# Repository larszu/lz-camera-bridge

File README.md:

# LZ Camera Bridge

A universal camera-control hub. One software interface — a broadcast-style
**RCP** (paint controls) and a touch **PTZ panel** modelled on the Panasonic
AW‑RP150 — plus a normalizing **command bus** that drives cameras from many
vendors over their native protocols. The same commands also reach every camera
from a Bitfocus **Companion** surface or a USB **control panel**.

> **Status:** the bridge, protocols and UI are real and build clean; a
> committed unit-test suite covers the protocol framing. Where a family was
> verified against public docs or an official reference it is marked
> **verified** below. Items marked *tuning* need a first on-camera test to
> confirm value encodings. Nothing ships as a fake/demo device.

## Download

**One installation is the whole tool.** The installer for Windows and macOS
carries the control surface *and* the bridge; the bridge starts with the
application, on `ws://localhost:9700`, and stops with it.

**https://github.com/larszu/lz-camera-bridge/releases**

That was not always true, and the difference matters if you read an older note:
until 2026-09-16 the installer shipped the panel alone. It came up looking
complete and reconnected every three seconds against a bridge that nobody had
started — you were expected to run a second process out of a clone of this repo,
and nothing in the application said so. Now the panel finds its bridge because
the application brought it.

A separate bridge is still perfectly legal, and for a control room it is the
normal case: run the bridge where the cameras are and point tablets at it (see
*Other devices on the same network*). If port 9700 is already taken the
application says so and uses the bridge that is already running, instead of
failing silently.

## The web page

Every push to the default branch builds this repo's page from
`.github/workflows/pages.yml` and publishes it:

**https://larszu.github.io/lz-camera-bridge/**

The workflow **asks the Pages API before it configures anything.** With no
Pages site it still builds — that is a real check — and skips only the
publishing step, with a warning and the one missing step in the run summary.
A run that must stay red for a click nobody made teaches people to ignore red.

Measured 2026-09-16: **published.** The Pages site exists, and the `deploy` job
now runs through — the switch that no workflow can flip (`GITHUB_TOKEN` may not
create a site) has been thrown. Every push to `main` publishes by itself.

What the page carries is the README and `docs/`, rendered — **not the UI
itself.** That is deliberate and not an omission: `web-rcp` is a client that
needs the bridge, and on a Pages address it would look like the application
while operating no camera. The running program comes from the installer below.

---
## Supported cameras

| Family | Mode | Transport | Status |
|---|---|---|---|
| Sony CCU (HXC/HDC, BRC) | `tcp` / `serial` | 700PTP over TCP :7700 / RS‑422 | paint verified; AWB/ABB deliberately disabled¹ |
| Sony FX / Alpha (FX3, FX6, A7 …) | `sony-usb` | PTP vendor extension over USB (libusb) | **verified** (codes from libgphoto2); handshake 3.00 and confirmed writes ported³ |
| Sony FX / Alpha over Wi-Fi/LAN | `sony-ptpip` | PTP/IP TCP 15740, SSDP discovery; Access Authentication through SSH (port 22, aes128-ctr, host-key fingerprint) | protocol **verified on an FX3 (fw 7.00)**³; this bridge path read-only on that FX3 |
| Sony Monitor & Control (FX WiFi) | `sony-mnc` | HTTP :10000 + SSDP discovery | unverified (undocumented app protocol) — for FX3/A7 prefer `sony-ptpip` |
| Canon EOS (R5/R6/R7/R8/R10 …) | `canon-ccapi` | CCAPI HTTP REST :8080 | **verified** (official CCAPI) |
| Panasonic Lumix (S1/S5/GH5/GH6 …) | `lumix-http` | `cam.cgi` HTTP | verified |
| Blackmagic (Pocket/Studio/URSA, FW 8.6+) | `blackmagic` | `/control/api/v1` REST + WS | **verified** |
| Z CAM (E2 family) | `zcam` | `/ctrl/set` HTTP | verified |
| Panasonic AW PTZ (AW‑UE/HE) | `panasonic-ptz` | `aw_ptz` / `aw_cam` CGI | **verified** (AW protocol) |
| VISCA over IP (PTZOptics, Marshall, AVer, Sony BRC/SRG) | `visca` | UDP :1259 (raw) / :52381 (Sony header) | **verified** |
| HTTP-CGI PTZ (Vissonic/PTZOptics `ptzctrl.cgi`, Sony SRG/BRC `/command/`) | `http-cgi` | HTTP GET, Referer + Digest; power via VISCA TCP :5678 (Vissonic) or `main.cgi` (Sony) | **verified** live on a Vissonic clone and a Sony SRG-A40 |
| JVC ConnectedCam / KY‑PZ | `jvc` | Digest login + `/cgi-bin/api.cgi` | verified vocabulary (some steps *tuning*) |
| BirdDog NDI PTZ | `birddog` | VISCA :52381 + REST :8080 | verified endpoints (*tuning*) |
| VISCA on a serial line (same heads, RS‑232/422 wiring) | `visca-serial` | RS‑232 8N1, 9600 default, daisy‑chain address 1–7 | framing unit‑tested; *not yet on a camera* |
| DJI Ronin RS 2 / RS 3 Pro | `dji-ronin` | DJI R SDK over CAN 1 Mbit/s via USB SLCAN adapter | framing unit‑tested; *not yet on a gimbal*² |
| DJI Osmo Pocket 3 / 4 | `dji-osmo` | DUML over a serial (CDC) device | framing unit‑tested; *not yet on a gimbal*³ |

³ Sony PTP, shared by `sony-usb` and `sony-ptpip` (`SonyPtpClient`), follows
Sony's *Camera Control PTP 3 Reference*: handshake with protocol 3.00 and
retry while the camera has no version yet; every write waits until the camera
reports the value (a real FX3 shows it ~250 ms late); 500 ms after an
exposure-mode change; the clock (0xD223) as an ISO 8601 string. The protocol
code is the one [lz-camera-sync](https://github.com/larszu/lz-camera-sync)
runs against an FX3 (fw 7.00) since 2026-10-07 — reading 369 properties,
writing and restoring values, setting the clock, over Wi-Fi with SSH. In this
bridge the `sony-ptpip` path was checked read-only against that FX3 (SSDP
found it and an A7 IV; SSH with fingerprint, handshake, 369 properties). The
SSH password is never written to `site.json`; after a bridge restart it is
entered again.

¹ Sony's 700 protocol is NDA-only; no public source documents the auto‑setup
command codes, so those buttons stay disabled rather than guessing at a
broadcast CCU. See `packages/web-rcp/src/capabilities.ts`.

² **RS 2 and RS 3 Pro only.** RS 3 and RSC 2 look the same and do not speak the
SDK. Needs a USB SLCAN adapter (CANable, USBtin, Lawicel) on the focus‑wheel
port — not SocketCAN, which is Linux‑only.

³ DJI publishes no control interface for the Pocket series, and its USB‑C port
serves storage and UVC webcam — **there is no USB control path.** The one
publicly reverse‑engineered route is Bluetooth LE; what ships here is DUML over
a serial device, and the BLE seam is prepared but not filled. Both gimbals move
the head only: a gimbal carries a camera, it is not one, so paint controls stay
greyed out. The full picture, including which constants to turn first if a
device stays silent, is in [`docs/dji-gimbal.md`](docs/dji-gimbal.md).

## Control surfaces

- **Web RCP** — Sony-style paint panel (iris, master black/gamma, R/G/B white &
  black balance, gain, ND, shutter, bars). Buttons are gated per backend so
  unsupported functions are disabled, not silently failing.
- **Touch PTZ panel** — AW‑RP150-style joystick (pan/tilt with speed),
  zoom/focus rockers, push‑AF, iris and a paged preset grid with a store mode.
- **Soft presets** — on heads that position absolutely and report their pose
  (VISCA IP/RS‑232, BirdDog, Panasonic AW, HTTP‑CGI, robotic heads) a stored
  preset keeps the pose in the bridge, and a recall glides there with
  ease‑in/out: all axes start and land together, move time per preset, *Soft*
  switch per preset. Other paths recall the camera's own preset, and the
  panel says so.
- **Bitfocus Companion** — module in `packages/companion-module-lz-camera-bridge`
  (v0.2.0): paint, pan/tilt/zoom/focus and the elevation column, soft presets
  (move time, *Soft* per preset), studio shots (cut/fade, shot sets, seats,
  moves, *move anyway*, on-air lock per camera), panorama aim and the switcher,
  with dropdowns, feedbacks, variables and ready-made button pages built from
  the bridge's cameras and studio shots. It talks to the Companion API
  (9701/9702) and the panel's port (9700). See its
  [`HELP.md`](packages/companion-module-lz-camera-bridge/companion/HELP.md).
- **USB HID control panel** — a data-driven adapter maps a hardware panel's
  axes/buttons onto the command bus, so one panel controls any brand.
- **Keyboard** — on the PTZ panel the arrow keys drive while held, `1`–`9`
  recall presets, `Home` goes home; a window that loses focus stops the head.
- **Planned shots** — the MultiCam Planner's camera list (v3) carries each
  camera's heading and its shots as pan/tilt/focal length in the room frame.
  The bridge turns them into head angles, drives them (`ptzAbsolute` on
  VISCA, Sony CGI, Panasonic AW and the Vissonic heads via VISCA TCP),
  stores them in the head's own preset memory, and takes a one-time
  **offset** on site: steer the head onto one known shot, click *Head is
  here*, and the mounting error is applied to every shot. From then on any
  panel or Companion recalls them by number. Zoom from a focal length is
  estimated between the ends of the lens until a **zoom curve** is measured:
  drive the zoom to 0/25/50/75/100 %, read the focal length off the lens or
  the camera menu, *Record point*. Details in
  [`docs/camera-plan.md`](docs/camera-plan.md).
- **Aim by frame** — on the PTZ panel, drag a 16:9 frame in the camera's live
  picture: the bridge turns it into pan/tilt from the pose the head reports
  and into a zoom position from the field of view per zoom (datasheet wide/tele
  angles, sensor width + focal length, or measured by *Measure*: the head pans
  a little at five zoom positions and the bridge measures how far the picture
  moved). Heads that take a stream of positions glide there like a soft preset;
  the robotic head plays its own eased keyframes; the others drive their
  own absolute move. Needs a head that reports its pose and a stream address.
- **Panorama map** — *Scan panorama* steps the head through a pan/tilt grid at
  wide zoom, takes a picture at every stop and stitches an equirectangular map
  from the known poses (no feature matching). It is stored in the config
  directory (`panorama/cam-<n>.jpg`) and served at `/panorama/<n>.jpg`. A frame
  drawn on the map drives the head there, also while it stands at full tele;
  the live picture is shown in its place on the map. The map is a still —
  scan again when the room has changed.
- **Studio shots** (view *Shots*) — for every camera on the bridge:
  - *Cut* or *Fade*: cut recalls at the camera's own top speed; fade is a
    timed move with ease-in/out, pan, tilt and zoom arriving together —
    the same preset glide as above, with the move time of the recall. A
    planned shot glides from the pose the head reports; robotic heads play
    the time themselves. Where neither works the shot cuts, and the panel
    says so.
  - *Shot sets* — one button recalls a shot on several cameras with one
    common move time.
  - *On-air lock* — a camera whose switcher input is on programme does not
    move on a shot recall (sets, seats, moves, preset keys, Companion
    presets, planned shots); the banner offers *Move anyway*. Per camera,
    on by default.
  - *Seats* — a seating chart (rows × seats); each seat lists shots on one
    or more cameras, best first. A tap takes the first camera that is
    connected and not on air. Optionally a *room plan* instead of the
    grid: seats are dragged to where they are (a lectern, a sofa, a panel
    table), and *Place grid* lays out rows × seats as a quick start.
  - *Moves* — shots of one camera in a row, each with its own move time and
    an optional hold; any joystick touch stops the move.

  Shot sets, seats and moves live in the site file. Untested on real heads:
  so far all of it has only run against the demo camera.

## Control room: switcher, video wall, site

The bridge also drives the room around the cameras. This came over from the
former `av-control-center` application (2026-09-28) and replaces it.

- **Switcher** — a Vissonic **VIS-CATC** (one output, twelve multi-image
  layouts) operated the way a panel works: a programme row over a preview row
  and one **CUT**. The preview bus lives in the bridge, so every screen shows
  the same pre-selection. Keys: `1`–`6` preview, `Shift`+digit take, `Enter`
  or `Space` cut — by key *code*, so it works on every keyboard layout. Two
  routes to the device, chosen per site: its network page (`POST /`) or the
  RS-232 verb list from the manual, through a TCP-serial gateway or a port on
  the bridge computer. Layouts, audio, freeze (serial only), a crosspoint list
  for multi-window layouts. Protocol in [`docs/switcher.md`](docs/switcher.md).
- **Tally per camera** — each camera names its switcher input; the bridge
  derives programme/preview from the switcher and shows it on the camera list,
  the wall, the PTZ panel and the video tiles. Companion gets
  `switcherPreview`, `switcherTake`, `switcherCut`.
- **Video** — live tiles from each camera's stream address (RTSP, SRT or
  RTMP). The bridge runs one ffmpeg per stream and serves `GET /video/<n>.mjpeg` on its own port; the
  page shows it in an ``, no player. Click a tile to preview its input,
  double-click to take. *Own window* opens the tiles alone for a second
  screen. The stream address never leaves the bridge. ffmpeg is looked for
  in `LZ_BRIDGE_FFMPEG`, `ffmpeg-portable/`, then `PATH`; the desktop app
  brings its own. **SRT needs an ffmpeg built with libsrt** — the bundled
  one and Homebrew's default formula have none (RTSP and RTMP work with
  both); the tile says so instead of staying black.
- **Scopes** — *Scopes* on a video tile opens waveform (luma) and
  vectorscope under it; each panel's header switches to RGB parade,
  histogram, CIE and more, *4 scopes* fills the window with waveform,
  vectorscope, parade and histogram. They measure raw R'G'B' frames from
  `WS /scope/<n>` (LZ Scopes frame protocol), not the JPEG of the tile: the
  bridge starts its own ffmpeg per open scope and stops it when the panel
  closes. Details in [`docs/live-video.md`](docs/live-video.md#scopes).
- **Site** — cameras and switcher as one file (`lz-site` v1). The desktop app
  and `npm run bridge` keep it in `LZ_BRIDGE_CONFIG_DIR/site.json`
  (default `~/.lz-camera-bridge`) and restore it on start, connecting what was
  connected. Export downloads it; import replaces the room — also from the
  settings export of the old av-control-center, so an existing room moves
  with one file. The file carries the camera logins; keep it out of
  repositories.
- **FreeD tracking** — every camera that reports its pose (VISCA, Panasonic
  AW, HTTP-CGI, robotic heads incl. elevation column) streams pan, tilt, zoom
  and focus as FreeD D1 over UDP to one or more receivers, e.g. Unreal Live
  Link: one switch per camera, targets and rate under *Site*, interpolated
  between pose reads, silent when a camera stops answering. Not yet tested
  against Unreal or real heads. Details in
  [`docs/freed-tracking.md`](docs/freed-tracking.md).

### Screens

| | |
|---|---|
|  |  |
| **Switcher** — PGM over PVW, CUT, layouts, audio | **Video** — live tiles from RTSP/RTMP/SRT, tally on the top edge |
|  |  |
| **Wall** — every camera's panel at once | **Site** — the room as one file |

Taken 2026-09-29 against demo cameras, a switcher stand-in and ffmpeg test
patterns streamed over RTMP — no real room, so nothing to blank out.

## Architecture

```
Input surfaces                 Bridge :9700 (command bus)          Devices
────────────────               ──────────────────────────          ───────
Web panel   ─┐                                                     ┌─ Sony CCU (700PTP) · Sony USB (PTP)
Cameras/Wall ┼─ WebSocket ────▶  BridgeServer                      ├─ Canon CCAPI · Lumix · Z CAM · Blackmagic
Switcher     ┤                   camera slots ──(RCP verbs)───────▶├─ VISCA (IP / RS-232) · Panasonic AW · JVC · BirdDog
Video tiles ─┼─ GET /video/n ─▶  RtspHub (ffmpeg → MJPEG) ◀────────┤  RTSP streams
Scopes       ┼─ WS /scope/n ──▶  ScopeStream (ffmpeg → raw RGBA) ◀─┤
Site        ─┘  GET /site.json   site file (persisted)             ├─ HTTP-CGI PTZ (Vissonic/PTZOptics, Sony SRG)
Companion   ── HTTP/WS :9701-2   switcher slots ──(route/cut)─────▶└─ Vissonic VIS-CATC (HTTP or RS-232)
HID panel   ── USB                 └─ tally per camera ──▶ every client
```

Every camera backend exposes the same `handleRcpCommand(cmd, params)` contract,
so a single command vocabulary (`setIris`, `setMasterGain`, `ptz`,
`recallPreset`, `home`, `setCameraPower`, …) fans out to all of them. A switcher
is not a camera and has its own slot family and verbs (`preview`, `cut`, `take`,
`route`, `setLayout`); the bridge derives the tally per camera from both. A visual walk-through lives in
[`docs/architecture.html`](docs/architecture.html).

Paint values can be trimmed relatively (`cmd: 'nudge'`) instead of only jumped
to: one resolution for every path — WebSocket, Companion buttons, the RCP's
up/down selectors — against the value the bridge has actually read. Where it has
read none, the trim is refused with a reason rather than started from a guessed
128. The bus scale of every value, and what each backend makes of it, is
documented in [`docs/paint-nudge.md`](docs/paint-nudge.md).

Every paint value on the panel says where it comes from: read back from the
device, or merely the last thing the bridge sent. Which is which is decided per
field and per connection mode by a table that was read out of this repository's
own backends — five of the twelve paths read nothing back at all, and the panel
says so once at the top instead of marking twenty knobs. See
[`docs/value-origin.md`](docs/value-origin.md).

Live-video feasibility per camera family — which cameras can show a live
picture in the panel, at what cost — is documented in
[`docs/live-video.md`](docs/live-video.md).

A USB control surface drives the bridge instead of the other way round: a
gamepad, or a panel you build yourself. A PlayStation controller is recognised
by vendor/product id and gets a *drive* mapping (left stick pan/tilt, analog
triggers zoom, face buttons presets); anything unknown keeps the *paint*
mapping it always had. That split is a safety boundary and not a convenience —
`setIris` is a 9-byte VISCA packet whose bytes 6/7 the DigitalBird DB3 decoder
reads as a pan/tilt direction, so a stick on iris makes that head drive off.
The parts list for a panel of your own, and the compatibility check against the
DB3 head, are in [`docs/ptz-pult-hardware.md`](docs/ptz-pult-hardware.md); the
two things that still need a real device are in
[`docs/ptz-pult-messprotokoll.md`](docs/ptz-pult-messprotokoll.md).

The bridge reads the `camera-list` the AV Planner Suite's MultiCam Planner
exports and holds it against the cameras on the bus, so the control wall can
label a slot the way the show calls it ("CAM 3 — Bühne links") instead of by
number. Every match carries evidence — a measured model, a mere convention, or a
human — and where there is none, there is no match. See
[`docs/camera-plan.md`](docs/camera-plan.md).

A B4 lens reports its name, open f-number, focal lengths and MOD over the
serial protocol. Those are **readings from one piece of glass**, not
capabilities of this repo, so they stay out of the `caps:parity` contract — the
reasoning, and where they live instead, is in
[`docs/b4/lens-facts-vs-capabilities.md`](docs/b4/lens-facts-vs-capabilities.md).

A zoom or focus demand wired to the B4 interface becomes an input on the same
bus: its wiper drives `setZoom`/`setFocus` on a chosen camera, through a table
measured on that demand, and an unplugged demand stops the axis instead of
holding its last value. Without the bridge the same firmware can appear as a
USB gamepad. See [`docs/b4/demand.md`](docs/b4/demand.md).

## Packages

| Path | What it is |
|---|---|
| `packages/bridge` | Node/TypeScript bridge server, camera clients, protocols, HID input, switcher (`src/switcher`), video hub (`src/multiview`), site file (`src/site`) |
| `packages/web-rcp` | React UI: Cameras (RCP + PTZ panel, wizard), Wall, Switcher, Video, Site |
| `packages/companion-module-lz-camera-bridge` | Bitfocus Companion module |
| `packages/electron-app` | Desktop application: the web UI **and** the bridge, bundled into one installer |
| `packages/firmware` | WIZ108SR serial↔TCP bridge firmware (C) |

**Source language:** `en`. New user-facing text goes in English. That is not a
preference but a measurement: the UI already carries roughly 140 English spots
against 32 German ones, and its vocabulary is the technical one anyway — Iris,
Gain, ND, Paint. Rewriting the English into German to then put „Blende" next to
`WB` costs work and makes the result worse. Decided 2026-09-08 (E-17);
`multicam-planner` is English-source as well, while `cable-planner` and
`light-planner` are German-source. The machine-readable copy of this
declaration sits in `package.json` under `avplan.sourceLanguage`.

The German spots that are still there are a **mixed-language product**, not a
translation backlog — the same dialog shows both. `npm run lang:check` counts
them and holds the count at the level measured when the check was introduced:
while that cleanup is open, the existing ones may stay, but the mix must not
grow. Translating some means lowering the limit in the same commit.

## Getting started

```bash
npm install            # workspaces install
./dev.sh               # Linux / macOS — bridge + web UI, demo camera preselected
npm run dev            # the same via npm (bridge backgrounded with `&`)
npm test               # protocol framing unit tests
```

### Try it without a camera

Pick the **Demo (no camera)** tab in the connection panel and connect. The
panel then talks to a state held in the bridge: move a control and the value
follows, so the surface — RCP, joystick, layout — can be tried on a laptop.

Before this, `npm run dev` always started but could not *show* anything:
every backend in `backendFactory` needs a real address (a CCU on TCP, a VISCA
port, a USB device in PC-Remote mode). Without one the panel came up empty
and every control was inert.

**It is not a camera simulator.** Nothing drifts, nothing is measured, and
every value moved because a command moved it. The state carries an `isDemo`
flag all the way to the dashboard, so a demo value can never be mistaken for
a reading from a real device — that is the same line `valueOrigin.ts` draws
between *commanded* and *confirmed*, and `test/demoKamera.test.ts` holds it:
one case asserts that nothing changes over 600 ms with no command, another
that `isDemo` survives `mapState`.

`dev.sh` also cleans up after itself. `npm run dev` appends the bridge with
`&` and leaves it: a Ctrl-C ends only the web UI, the bridge stays on port
9700, and the next start fails on it.

### Other devices on the same network

The bridge binds every interface and now prints the addresses you can hand
out, not just `localhost`:

```
[BridgeServer] WebSocket listening on ws://localhost:9700
[BridgeServer]                     ws://192.168.1.42:9700  (same network)
```

All detected addresses are listed rather than one being guessed: on a machine
with a Docker or VPN bridge the first one is often the wrong one.

Build individually:

```bash
npm run build --workspace=packages/bridge
npm run build --workspace=packages/web-rcp
```

Optional native modules (loaded lazily, not required to build/run):

```bash
npm install usb      --workspace=packages/bridge   # Sony USB (PTP) discovery/control
npm install node-hid --workspace=packages/bridge   # USB control-panel input
```

## First run

Open the web UI and follow the setup wizard: pick a camera family, enter its
address (the wizard shows the right defaults per protocol), and connect. PTZ
cameras open the joystick panel automatically; paint cameras open the RCP.

The header switches between five views: **Cameras** (one camera, its
connection and panel), **Wall** (every camera's panel at once), **Switcher**,
**Video** and **Site**. Under *Cameras* every camera also takes a name, its
RTSP stream address and its switcher input — that is all the Video and
Switcher views need. A room that already exists as a site file goes in under
*Site → Import*; the bridge then connects everything by itself.

- **Sony BRC/SRG PTZ:** choose the *VISCA over IP* tab and set port **52381** —
  the Sony transport header is applied automatically. Where the room blocks
  the VISCA ports, the *HTTP-CGI PTZ* tab drives the same head over its web
  CGI (family *Sony*, login required; power is read back). Over this CGI the
  Sony also takes manual white balance: R and B gain (`imaging.cgi`
  `WhiteBalanceCrGain`/`CbGain`, read back from `inquiry.cgi?inq=imaging`).
  It has no G gain and, over the CGI, no hue, saturation, black or gamma.
- **Vissonic / PTZOptics PTZ:** *HTTP-CGI PTZ*, family *Vissonic*. No login
  for control; power on/standby goes over VISCA TCP 5678 and is read back.
  Stream address `rtsp://<ip>:554/1`.
- **VIS-CATC switcher:** the *Switcher* view, *+ Switcher*, address of the
  device page. Give each camera its switcher input in the connection panel.
- **Sony FX/Alpha USB:** put the camera in *PC Remote* mode; install the `usb`
  module on the host.
- **Canon:** activate CCAPI once via Canon's tool, then enter the shown IP/port.
- **VISCA on a cable:** the *VISCA RS‑232* tab. Most heads ship at 9600 baud,
  address 1. Not the same as the *8‑Pin RS‑422* tab next to it — that is Sony's
  9‑pin protocol on a different cable with different framing (odd parity).
- **DJI gimbals:** the *DJI Ronin* and *DJI Osmo Pocket* tabs move the head
  only. Read [`docs/dji-gimbal.md`](docs/dji-gimbal.md) first — it says what is
  proven and what is not, and there is no USB control path for the Pocket.

## License

Proprietär — © 2026 Lars Zumpe, alle Rechte vorbehalten. Nutzung der veröffentlichten Builds ist kostenlos; Weiterverbreitung und abgeleitete Werke sind es nicht. Siehe [LICENSE](LICENSE).

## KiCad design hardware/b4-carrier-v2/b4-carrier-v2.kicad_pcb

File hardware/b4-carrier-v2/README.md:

# B4 lens carrier board v2

135 × 92 mm, 4 layers (GND poured on every layer), SMD assembled by PCBWay, two 18650
cells on the bottom. Successor of [v1](../b4-carrier/README.md): same analog
stages (measured on the bench on 2026-10-10, simulated in
[`../b4-carrier/simulation/`](../b4-carrier/simulation/README.md)), but every
chip is on the board and the board runs on its battery.

**Status: draft, not ordered, nothing powered.** Fully routed. KiCad DRC
(zones refilled): 0 unconnected, 0 clearance, 0 silkscreen errors; the only
entries are the four intended overlaps of the fused ESP32 header courtyards.
The netlist lives in `generate_pcb.py` (one `place()` / `R()` / `C()` call per
part with its nets); there is no `.kicad_sch`.

## Rules and current paths

| Rule | Value |
|---|---|
| Clearance | 0.15 mm (signals), 0.2–0.25 mm for pours and power trunks |
| Track / via minimum | 0.12 mm / 0.45 mm via, 0.2 mm drill (PCBWay standard) |
| Copper to board edge | 0.5 mm; trunks keep ≥ 1.2 mm |
| Main current paths (B.Cu trunks, `power_trunks.py`) | 2.0 mm: VBAT_RAW, VMID, VBAT, CHG_IN, VSYS · 1.5 mm: V12, V12_LENS, DC_IN, USB_VBUS · 1.0 mm: ESP_5V — each with a via cluster at its capacitor |
| Power pours (`postprocess.py`) | every power track gets a 1.5 mm (0.8 mm for 5 V / 9 V) pour along it, clipped where other copper is near |
| Width check | `width-report.txt`: narrowest copper per power net away from pads |

Sized for 1.5 A lens current from 2S cells (6–8.4 V): VSYS / VBAT then carry up
to ≈ 3.5 A; 2 mm on 35 µm outer copper is ≈ 4 A at 20 K rise (IPC-2152,
estimate, not measured). The trunks also end directly on via groups at the
BQ25798's VBAT and CHG_IN pins and at the eFuse input. Narrow entries left in
`width-report.txt` are branches that carry no load current (test points,
balancer sense line) and the SW1 / SW2 stubs right at the BQ25798 pins, which
cannot be wider than the 0.25 mm pins themselves.

The charger core is laid out by hand (`charger_core()`): U2 turned so SW1/SW2
face L1 directly, PMID and SYS capacitors on short buses right at their pins,
the power-ground pin straight into the planes with two vias between SW1 and SW2,
PROG resistor directly at pin 20, charge LED at STAT. D+ and D− are tied at the
pins (BC1.2 "dedicated charger"): PD is negotiated by the CH224A, the input
current limit is set by the firmware.

## Blocks

| Block | Parts | Datasheet values used |
|---|---|---|
| Input | USB-C with **CH224A** (24 kΩ CFG1 → asks for 12 V) or DC jack 6–20 V, each through B540C, TVS SMBJ22A | CH224A table 5-1 |
| Charger | **BQ25798** buck-boost, 2S, NVDC: VSYS keeps running from the input while the cells charge; D+/D− tied at the pins (no USB data needed, PD is the CH224A's) | PROG 8.2 kΩ = 2S / 750 kHz, L 2.2 µH, TS divider 5.23k/30.1k + 10k NTC, BATP 100 Ω, SDRV 1 nF, VAC1/VAC2 on VBUS, ACDRV to GND (no input FETs) |
| Cells | 2 × Keystone 1042 (bottom), 5 A fuse, **BQ29209** overvoltage + balancing | OUT pulls CE high → charging stops on a cell overvoltage |
| 12 V | **TPS55340** boost from VSYS (6–8.4 V) | FB 88.7k/10k = 12.13 V, FREQ 78.7k = 600 kHz, L 10 µH, B540C |
| Lens protection | **TPS259541** eFuse: ~1.5 A limit, 13.7 V clamp, UVLO ≈ 10 V; `LENS_OFF` switches lens power off | ILM 1.40k, dVdt 22 nF |
| Lens current | **INA219** (0x40) over 20 mΩ | jammed servo or short shows up as current |
| 9 V / 5 V / 3.3 V | LM317 (9.06 V for LM324 + CD4066), AP63205 (5 V for ESP32 + remote), AP2112K-3.3 (quiet analog 3.3 V) | |
| Analog | MCP4728 (0x60), ADS1115 (0x48), LM324: iris stage as on the bench, zoom/focus `REF + 1.8·(V_B/D − V_C)` with 100k/180k | |
| Outputs off at start | **CD4066** in iris, zoom, focus and remote; closes only when the firmware sets `OUT_EN` | no twitch while the ESP32 boots |
| VTR / RET | On-board buttons, JST **BUTTONS** for external ones (with LED), lens grip pins 1/2 through Schottky (wired-OR) | |
| Tally | 2 × 12 V low-side outputs (AO3400, 0.5 A PTC), 1 optocoupled input (PC817, 5–24 V) | for box lenses / tally lamps |
| Pots | 3 on-board (Alps RK09K) + 3 JST, jumper per axis | |

## Connectors

| Ref | Label | Pins (1 → n) |
|---|---|---|
| J3 | LENS | 6 +12 V · 3 GND · 5 iris · 7 iris pos · 8 remote · 10 zoom pos · 11 focus pos · 1 RET · 2 VTR · 12 |
| J4 | ZOOM DEMAND | GND · 6 (speed) · 7 (5 V ref) · 9 (position) of the black grip socket |
| J5 | FOCUS DEMAND | GND · control · ref · position (**to be measured**) |
| J6 | OLED | GND · 3V3 · SCL · SDA |
| J20 | BUTTONS | 5 V · LED (cathode, 150 Ω on board) · VTR · RET · GND |
| J21 | TALLY | 12 V · red (low-side) · green (low-side) · IN+ · IN− |
| J22–J24 | EXT POT | 3V3 · wiper · GND |

## ESP32: one block, two boards

DevKit V1 rows at x0 and x0 + 22.86 / 25.40 / 27.94 mm (fit **one** of the
three VIN-row sockets); Waveshare ESP32-S3-ETH rows at x0 + 2.54 and
x0 + 20.32, turned 180° (RJ45 towards the bottom edge). **Fit only one board.**
The DRC reports the overlapping header courtyards — intended.

| Signal | DevKit GPIO | S3-ETH GPIO |
|---|---|---|
| SDA / SCL | 21 / 22 | 16 / 17 |
| Pot iris / zoom / focus | 34 / 35 / 36 | 1 / 2 / 3 |
| CHG_INT (charger) | 39 | 18 |
| OUT_EN (CD4066) | 25 | 15 |
| LENS_OFF (eFuse) | 26 | 38 |
| Tally red / green / in | 27 / 14 / 32 | 39 / 40 / 41 |
| Button VTR / RET / LED | 33 / 13 / 4 | 42 / 47 / 48 |
| eFuse fault | 16 | 44 |
| Status LED | 19 | 43 |

## Firmware this board needs

* `OUT_EN` high only after the DAC holds sane values (iris at the measured
  position, B = C = D = mid-scale).
* Zoom/focus: DAC C fixed at 2048, speed = DAC B/D − DAC C.
* BQ25798 over I²C (0x6B): watchdog off or fed, charge current, ADC for
  VBAT/VSYS; **ship mode below ~6.4 V pack** (cell undervoltage is software).
* INA219 lens current on the status page; `LENS_OFF` on overcurrent.
* Tally, VTR/RET, OLED.

## Regenerate

```
/Applications/KiCad/KiCad.app/Contents/Frameworks/Python.framework/Versions/3.9/bin/python3 \
    hardware/b4-carrier-v2/generate_pcb.py --route
```

Takes ~20 minutes. Steps:

1. `generate_pcb.py`: places the blocks (charger core by hand, a legaliser
   pushes passives off anything they land on and off the holder pegs), draws the
   charger fan-out, then `power_trunks.py` lays the wide power paths on B.Cu
   (grid router, locked).
2. Freerouting routes the rest on all four layers.
3. `fixup.py`: removes dead copper, routes what Freerouting left open with a
   clearance-checked four-layer grid router (rip-up and retry), removes stray vias.
4. `postprocess.py`: power pours, GND stitching vias, width report, moves
   reference designators to free spots (the ones that do not fit stay on F.Fab,
   i.e. in `fab/top-assembly.pdf`).

Freerouting is not deterministic: a new run gives a different (also DRC-clean,
check it) layout.

## Before ordering

1. Check every connector against the parts you have (OLED pin order varies).
2. Check the polarity print of the holders (pad 1 = +) and the cell orientation.
3. Run the DRC once more in KiCad after any change.
4. 4 layers, 1.6 mm, ENIG, SMT assembly top (`fab/bom-smt.csv`,
   `fab/cpl-smt.csv`); holders, headers, JSTs, pots and DC jack by hand.
5. Inductor saturation currents (L1 ≥ 8 A, L2 ≥ 6 A) are what matters when
   PCBWay offers alternatives.

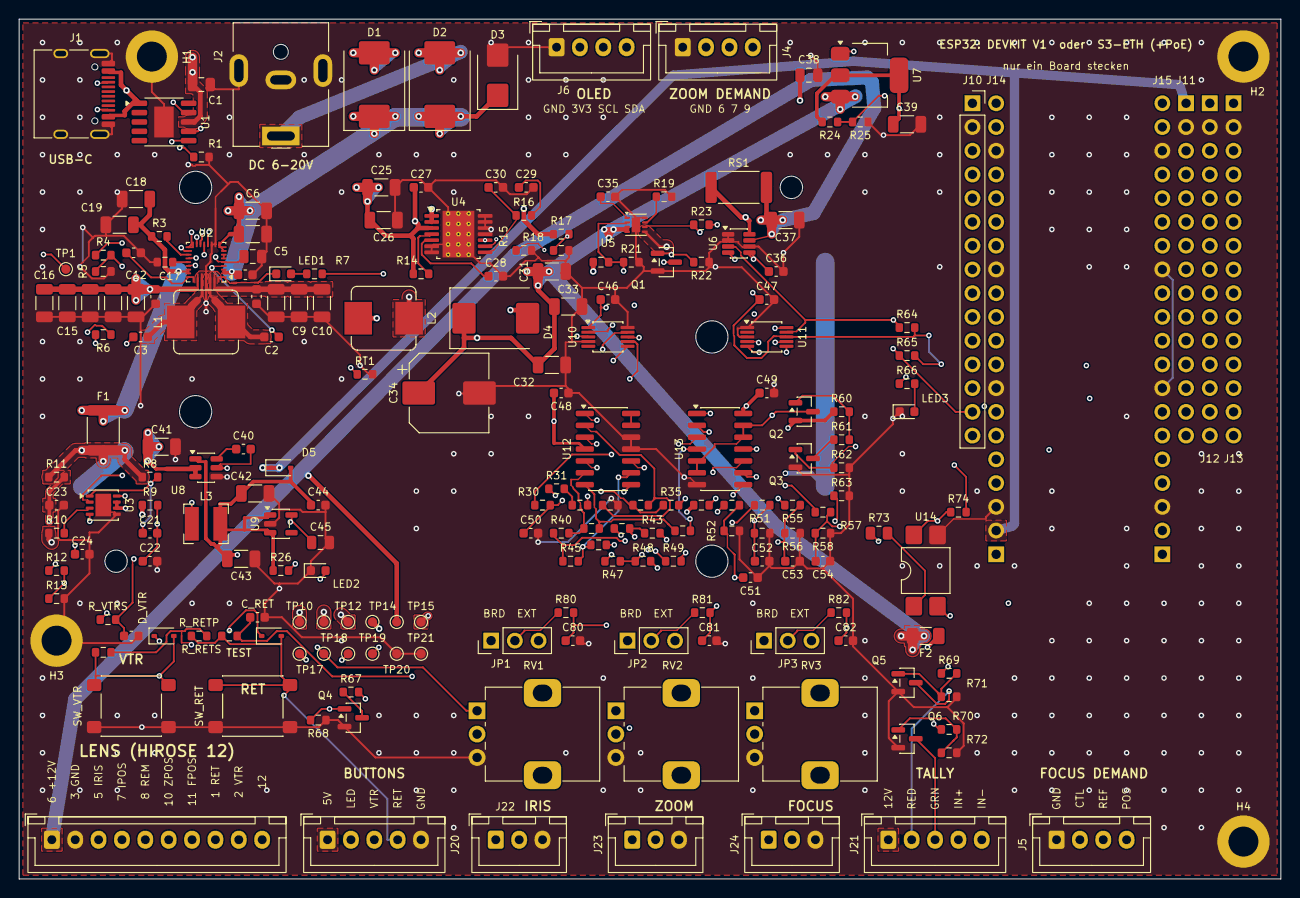
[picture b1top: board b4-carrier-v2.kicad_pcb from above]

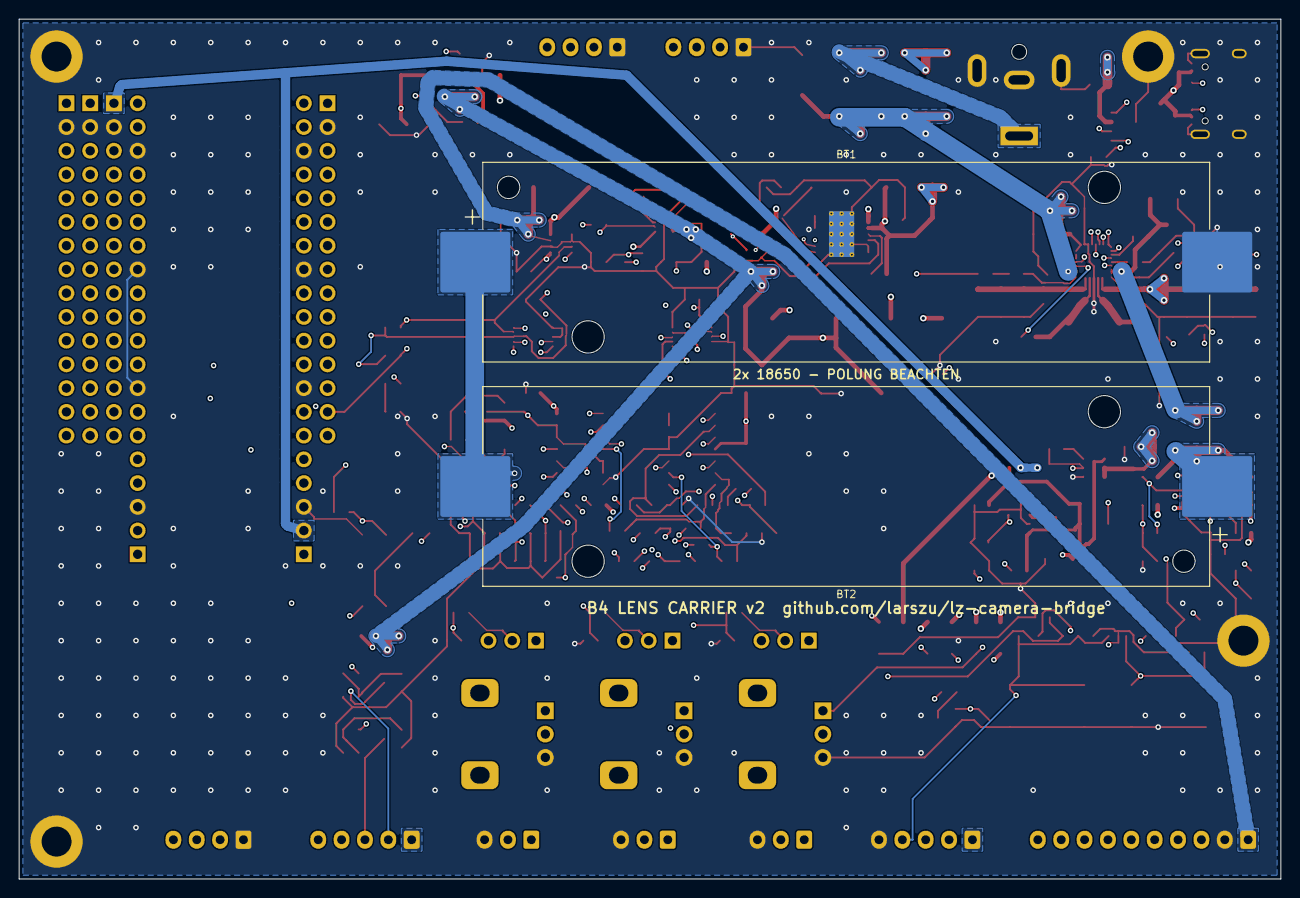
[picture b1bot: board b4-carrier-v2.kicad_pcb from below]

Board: 4 copper layers, 135.0 x 92.0 mm, 213 parts (2 on the bottom side), 128 nets.

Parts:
BT1: 18650 low; BatteryHolder_Keystone_1042_1x18650
BT2: 18650 high; BatteryHolder_Keystone_1042_1x18650
C1, C38: 1uF 25V; C_0805_2012Metric
C2, C3: 47nF 25V; C_0603_1608Metric
C4: 4.7uF 16V; C_0805_2012Metric
C5, C6, C8, C9, C10, C12, C13, C14, C15, C16, C18, C19, C25, C26, C31, C32, C33, C37, C39, C41: 10uF 25V; C_1206_3216Metric
C7, C11, C17, C27: 100nF 50V; C_0603_1608Metric
C20: 1nF 50V; C_0603_1608Metric
C21, C22, C23, C24, C29, C36, C40, C46, C47, C48, C49, C50, C51, C52, C53, C54, C80, C81, C82: 100nF; C_0603_1608Metric
C28: 47nF; C_0603_1608Metric
C30: 100pF; C_0603_1608Metric
C34: 100uF 25V; CP_Elec_8x10
C35: 22nF; C_0603_1608Metric
C42, C43: 22uF 10V; C_1206_3216Metric
C44: 1uF; C_0603_1608Metric
C45: 4.7uF; C_0805_2012Metric
C_RET: 100nF; C_0603_1608Metric
C_VTR: 100nF; C_0603_1608Metric
D1, D2, D4: B540C; D_SMC
D3: SMBJ22A; D_SMB
D5: BAT60A; D_SOD-323
D_RET: BAT54J; D_SOD-323
D_VTR: BAT54J; D_SOD-323
F1: 5A; Fuse_1812_4532Metric
F2: 0.5A PTC; Fuse_1206_3216Metric
H1, H2, H3, H4: M3; MountingHole_3.2mm_M3_DIN965_Pad
J1: USB-C PD/CHARGE; USB_C_Receptacle_HRO_TYPE-C-31-M-12
J2: DC 6-20V; BarrelJack_CUI_PJ-063AH_Horizontal
J3: LENS; JST_XH_B10B-XH-A_1x10_P2.50mm_Vertical
J4: ZOOM DEMAND; JST_XH_B4B-XH-A_1x04_P2.50mm_Vertical
J5: FOCUS DEMAND; JST_XH_B4B-XH-A_1x04_P2.50mm_Vertical
J6: OLED; JST_XH_B4B-XH-A_1x04_P2.50mm_Vertical
J10: DEVKIT 3V3 ROW; PinSocket_1x15_P2.54mm_Vertical
J11: DEVKIT VIN ROW 22.86; PinSocket_1x15_P2.54mm_Vertical
J12: DEVKIT VIN ROW 25.40; PinSocket_1x15_P2.54mm_Vertical
J13: DEVKIT VIN ROW 27.94; PinSocket_1x15_P2.54mm_Vertical
J14: S3-ETH VBUS ROW; PinSocket_1x20_P2.54mm_Vertical
J15: S3-ETH IO20 ROW; PinSocket_1x20_P2.54mm_Vertical
J20: BUTTONS; JST_XH_B5B-XH-A_1x05_P2.50mm_Vertical
J21: TALLY; JST_XH_B5B-XH-A_1x05_P2.50mm_Vertical
J22: EXT POT I; JST_XH_B3B-XH-A_1x03_P2.50mm_Vertical
J23: EXT POT Z; JST_XH_B3B-XH-A_1x03_P2.50mm_Vertical
J24: EXT POT F; JST_XH_B3B-XH-A_1x03_P2.50mm_Vertical
JP1: POT I; PinHeader_1x03_P2.54mm_Vertical
JP2: POT Z; PinHeader_1x03_P2.54mm_Vertical
JP3: POT F; PinHeader_1x03_P2.54mm_Vertical
L1: 2.2uH; L_Bourns_SRP7028A_7.3x6.6mm
L2: 10uH; L_Bourns_SRP7028A_7.3x6.6mm
L3: 4.7uH; L_Bourns-SRN4018
LED1: CHG; LED_0603_1608Metric
LED2: PWR; LED_0603_1608Metric
LED3: STATUS; LED_0603_1608Metric
Q1, Q3, Q4, Q5, Q6: AO3400A; SOT-23
Q2: AO3401A; SOT-23
R1: 24k; R_0603_1608Metric
R2: 8.2k; R_0603_1608Metric
R3, R11, R69, R70: 100; R_0603_1608Metric
R4: 5.23k; R_0603_1608Metric
R5: 30.1k; R_0603_1608Metric
R6, R18, R23, R30, R31, R33, R34, R61, R74: 10k; R_0603_1608Metric
R7, R8, R9, R26, R35, R50, R80, R81, R82: 1k; R_0603_1608Metric
R10: 910; R_0603_1608Metric
R12, R14, R20, R22, R40, R42, R45, R47, R51, R53, R55, R57, R60, R62, R63, R68, R71, R72: 100k; R_0603_1608Metric
R13: 47k; R_0603_1608Metric
R15: 78.7k; R_0603_1608Metric
R16: 2k; R_0603_1608Metric
R17: 88.7k; R_0603_1608Metric
R19: 1.4k; R_0603_1608Metric
R21: 13.7k; R_0603_1608Metric
R24: 240; R_0603_1608Metric
R25: 1.5k; R_0603_1608Metric
R32: 5.6k; R_0603_1608Metric
R41, R43, R46, R48: 180k; R_0603_1608Metric
R44, R49: 1.2k; R_0603_1608Metric
R52, R54, R56, R58: 68k; R_0603_1608Metric
R64, R65: 4.7k; R_0603_1608Metric
R66: 330; R_0603_1608Metric
R67: 150; R_0603_1608Metric
R73: 2.2k; R_0805_2012Metric
RS1: 20mR; R_2512_6332Metric
RT1: 10k NTC 103AT; R_0603_1608Metric
RV1: 10k IRIS; Potentiometer_Alps_RK09K_Single_Vertical
RV2: 10k ZOOM; Potentiometer_Alps_RK09K_Single_Vertical
RV3: 10k FOCUS; Potentiometer_Alps_RK09K_Single_Vertical
R_RETP: 10k; R_0603_1608Metric
R_RETS: 1k; R_0603_1608Metric
R_VTRP: 10k; R_0603_1608Metric
R_VTRS: 1k; R_0603_1608Metric
SW_RET: RET; SW_SPST_PTS645Sx43SMTR92
SW_VTR: VTR; SW_SPST_PTS645Sx43SMTR92
TP1: QON; TestPoint_Pad_D1.0mm
TP10: CHG_IN; TestPoint_Pad_D1.0mm
TP11: VSYS; TestPoint_Pad_D1.0mm
TP12: VBAT; TestPoint_Pad_D1.0mm
TP13: V12; TestPoint_Pad_D1.0mm
TP14: V12_LENS; TestPoint_Pad_D1.0mm
TP15: V9; TestPoint_Pad_D1.0mm
TP16: V5; TestPoint_Pad_D1.0mm
TP17: A3V3; TestPoint_Pad_D1.0mm
TP18: IRIS_CTRL; TestPoint_Pad_D1.0mm
TP19: ZOOM_CTRL; TestPoint_Pad_D1.0mm
TP20, TP21: GND; TestPoint_Pad_D1.0mm
U1: CH224A; SSOP-10-1EP_3.9x4.9mm_P1mm_EP2.1x3.3mm
U2: BQ25798; Texas_RQM0029A_VQFN-29_4x4mm_P0.4mm
U3: BQ29209; VSON-8-1EP_3x3mm_P0.65mm_EP1.65x2.4mm
U4: TPS55340; Texas_HTSSOP-14-1EP_4.4x5mm_P0.65mm_EP3.4x5mm_Mask2.94x3.34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
U5: TPS259541; Texas_DSG0008A_WSON-8-1EP_2x2mm_P0.5mm_EP0.9x1.6mm
U6: INA219; SOT-23-8
U7: LM317; SOT-223-3_TabPin2
U8: AP63205; SOT-23-6
U9: AP2112K-3.3; SOT-23-5
U10: MCP4728; MSOP-10_3x3mm_P0.5mm
U11: ADS1115; MSOP-10_3x3mm_P0.5mm
U12: LM324; SOIC-14_3.9x8.7mm_P1.27mm
U13: CD4066B; SOIC-14_3.9x8.7mm_P1.27mm
U14: PC817; SMDIP-4_W7.62mm

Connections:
A3V3: C36.1, C45.1, C46.1, C47.1, J6.2, J22.1, J23.1, J24.1, R6.2, R7.1, R23.2, R31.1, R64.2, R65.2, R74.2, RV1.1, RV2.1, RV3.1, R_RETP.2, R_VTRP.2, TP17.1, U6.5, U9.5, U10.1, U11.8
ADC0: C52.1, R53.2, R54.1, U11.4
ADC1: C53.1, R55.2, R56.1, U11.5
ADC2: C54.1, R57.2, R58.1, U11.6
ADC3: C51.1, R51.2, R52.1, U11.7
B5_BST: C40.1, U8.6
B5_SW: C40.2, L3.1, U8.5
BAL_CB: R10.2, U3.3
BAL_CD: C24.1, U3.4
BAL_OUT: R12.1, U3.8
BAL_VC1: C21.2, C22.1, R9.2, U3.2
BAL_VC2: C21.1, R8.2, U3.1
BAL_VDD: C23.1, R11.2, U3.6, U3.7
BATP: R3.2, U2.18
BST_COMP: C30.1, R16.1, U4.8
BST_EN: R14.2, U4.4
BST_FB: R17.2, R18.1, U4.9
BST_FREQ: R15.1, U4.10
BST_RC: C29.1, R16.2
BST_SS: C28.1, U4.5
BST_SW: D4.2, L2.2, U4.1, U4.2
BTN_LED: J10.5, J15.4, Q4.1, R68.1
BTN_LED_D: Q4.3, R67.1
BTN_LED_K: J20.2, R67.2
BTN_RET: C_RET.1, J11.3, J12.3, J13.3, J15.5, R_RETS.2
BTN_RET_RAW: D_RET.2, J20.4, R_RETP.1, R_RETS.1, SW_RET.1
BTN_VTR: C_VTR.1, J11.9, J12.9, J13.9, J15.9, R_VTRS.2
BTN_VTR_RAW: D_VTR.2, J20.3, R_VTRP.1, R_VTRS.1, SW_VTR.1
BTST1: C2.1, U2.4
BTST2: C3.1, U2.19
CC1: J1.A5, U1.7
CC2: J1.B5, U1.6
CHG_CE: R12.2, R13.1, U2.13
CHG_DPDM: U2.6, U2.7
CHG_IN: C5.1, C6.1, C7.1, D1.1, D2.1, D3.1, TP10.1, U2.2, U2.3, U2.8, U2.9
CHG_INT: J11.13, J12.13, J13.13, J14.10, R6.1, U2.21
CHG_STAT: LED1.1, U2.1
DAC_A: R30.1, U10.6
DAC_B: R42.1, U10.7
DAC_C: R40.1, R45.1, U10.8
DAC_D: R47.1, U10.9
DC_IN: D2.2, J2.1
D_OUT: U12.13, U12.14
EF_DVDT: C35.1, U5.1
EF_EN: Q1.3, R20.2, R21.1, U5.2
EF_FLT: J10.6, J14.19, R23.1, U5.6
EF_ILM: R19.1, U5.7
ESP_5V: D5.1, J11.1, J12.1, J13.1, J14.2
EXT_F: J24.2, JP3.3
EXT_I: J22.2, JP1.3
EXT_Z: J23.2, JP2.3
FOCUS_CTRL: J5.2, U13.9
FOCUS_POS: J3.7, R57.1
FREF: J5.3, R48.2
F_N: R45.2, R46.1, U12.9
F_OUT: R46.2, R49.1, U12.8
F_P: R47.2, R48.1, U12.10
F_SW: R49.2, U13.8
GND: BT1.2, C1.2, C4.2, C5.2, C6.2, C7.2, C8.2, C9.2, C10.2, C11.2, C12.2, C13.2, C14.2, C15.2, C16.2, C17.2, C18.2, C19.2, C20.2, C22.2, C23.2, C24.2, C25.2, C26.2, C27.2, C28.2, C29.2, C30.2, C31.2, C32.2, C33.2, C34.2, C35.2, C36.2, C37.2, C38.2, C39.2, C41.2, C42.2, C43.2, C44.2, C45.2, C46.2, C47.2, C48.2, C49.2, C50.2, C51.2, C52.2, C53.2, C54.2, C80.2, C81.2, C82.2, C_RET.2, C_VTR.2, D3.2, H1.1, H2.1, H3.1, H4.1, J1.A1, J1.A12, J1.B1, J1.B12, J1.SH, J2.2, J2.MP, J3.2, J4.1, J5.1, J6.1, J10.2, J11.2, J12.2, J13.2, J14.3, J14.8, J14.13, J14.18, J15.3, J15.8, J15.13, J15.18, J20.5, J22.3, J23.3, J24.3, LED2.1, LED3.1, Q1.2, Q3.2, Q4.2, Q5.2, Q6.2, R1.2, R2.2, R5.2, R13.2, R15.2, R18.2, R19.2, R21.2, R22.2, R25.2, R33.2, R52.2, R54.2, R56.2, R58.2, R62.2, R63.2, R68.2, R71.2, R72.2, RT1.2, RV1.3, RV2.3, RV3.3, SW_RET.2, SW_VTR.2, TP20.1, TP21.1, U1.11, U2.10, U2.11, U2.27, U3.5, U3.9, U4.6, U4.7, U4.11, U4.12, U4.13, U4.14, U4.15, U5.8, U5.9, U6.1, U6.2, U6.6, U8.4, U9.2, U10.4, U10.10, U11.1, U11.3, U12.11, U12.12, U13.7, U14.3
IRIS_CTRL: J3.3, R51.1, TP18.1, U13.2
IRIS_POS: J3.4, R53.1
I_N: R33.1, R34.2, U12.2
I_OUT: R34.1, R35.1, U12.1
I_P: C50.1, R30.2, R32.2, U12.3
I_RA: R31.2, R32.1
I_SW: R35.2, U13.1
LDO_ADJ: R24.2, R25.1, U7.1
LED_CHG: LED1.2, R7.2
LED_PWR: LED2.2, R26.2
LED_ST: LED3.2, R66.2
LENS_OFF: J11.7, J12.7, J13.7, J15.14, Q1.1, R22.1
LENS_RET: D_RET.1, J3.8
LENS_VTR: D_VTR.1, J3.9
OUT_EN: J11.8, J12.8, J13.8, J14.12, Q3.1, R62.1
PD_CFG1: R1.1, U1.9
PF: JP3.2, R82.1
PI: JP1.2, R80.1
PMID: C8.1, C9.1, C10.1, C11.1, U2.29
POT_F: C82.1, J11.14, J12.14, J13.14, J14.14, R82.2
POT_I: C80.1, J11.12, J12.12, J13.12, J14.16, R80.2
POT_Z: C81.1, J11.11, J12.11, J13.11, J14.15, R81.2
PROG: R2.1, U2.20
PZ: JP2.2, R81.1
QON: TP1.1, U2.12
REGN: C4.1, R4.1, U2.5, U2.17
REMOTE: J3.5, U13.10
REM_SRC: R50.2, U13.11
RVFW: JP3.1, RV3.2
RVIW: JP1.1, RV1.2
RVZW: JP2.1, RV2.2
SCL: J6.3, J10.14, J14.7, R65.1, U2.14, U6.4, U10.2, U11.10
SDA: J6.4, J10.11, J14.9, R64.1, U2.15, U6.3, U10.3, U11.9
SDRV: C20.1, U2.24
STAT_LED: J10.10, J14.20, R66.1
SW1: C2.2, L1.1, U2.28
SW2: C3.2, L1.2, U2.26
SW_CTRL: Q2.3, R63.1, U13.5, U13.6, U13.12, U13.13
SW_G: Q2.1, R60.2, R61.2
SW_GD: Q3.3, R61.1
TALLY_G: J11.5, J12.5, J13.5, J15.11, R70.1
TALLY_G_D: J21.3, Q6.3
TALLY_G_G: Q6.1, R70.2, R72.1
TALLY_IN: J11.10, J12.10, J13.10, J15.10, R74.1, U14.4
TALLY_R: J11.6, J12.6, J13.6, J15.12, R69.1
TALLY_R_D: J21.2, Q5.3
TALLY_R_G: Q5.1, R69.2, R71.1
TALLY_V: F2.2, J21.1
TIN_A: R73.2, U14.1
TIN_N: J21.5, U14.2
TIN_P: J21.4, R73.1
TS: R4.2, R5.1, RT1.1, U2.16
USB_VBUS: C1.1, D1.2, J1.A4, J1.A9, J1.B4, J1.B9, U1.1, U1.8
V5: C42.1, C43.1, C44.1, D5.2, J20.1, L3.2, R26.1, R50.1, TP16.1, U8.1, U9.1, U9.3
V9: C39.1, C48.1, C49.1, Q2.2, R24.1, R60.1, TP15.1, U7.2, U12.4, U13.14
V12: C31.1, C32.1, C33.1, C34.1, C38.1, D4.1, F2.1, R17.1, R20.1, TP13.1, U5.3, U5.4, U7.3
V12E: RS1.1, U5.5, U6.8
V12_LENS: C37.1, J3.1, RS1.2, TP14.1, U6.7
VBAT: C18.1, C19.1, F1.2, R3.1, TP12.1, U2.22, U2.23
VBAT_RAW: BT2.1, F1.1, R8.1, R11.1
VMID: BT1.1, BT2.2, R9.1, R10.1
VSYS: C12.1, C13.1, C14.1, C15.1, C16.1, C17.1, C25.1, C26.1, C27.1, C41.1, L2.1, R14.1, TP11.1, U2.25, U4.3, U8.2, U8.3
ZOOM_CTRL: J4.2, TP19.1, U13.3
ZOOM_POS: J3.6, R55.1
ZREF: J4.3, R43.2
Z_N: R40.2, R41.1, U12.6
Z_OUT: R41.2, R44.1, U12.7
Z_P: R42.2, R43.1, U12.5
Z_SW: R44.2, U13.4

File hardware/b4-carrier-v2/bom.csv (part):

Ref,Value,Footprint,Part / MPN,Assembly,Note
"H1","M3","MountingHole:MountingHole_3.2mm_M3_DIN965_Pad","","hand",""
"H2","M3","MountingHole:MountingHole_3.2mm_M3_DIN965_Pad","","hand",""
"H3","M3","MountingHole:MountingHole_3.2mm_M3_DIN965_Pad","","hand",""
"H4","M3","MountingHole:MountingHole_3.2mm_M3_DIN965_Pad","","hand",""
"J1","USB-C PD/CHARGE","Connector_USB:USB_C_Receptacle_HRO_TYPE-C-31-M-12","HRO TYPE-C-31-M-12 (LCSC C165948)","SMT",""
"U1","CH224A","Package_SO:SSOP-10-1EP_3.9x4.9mm_P1mm_EP2.1x3.3mm","WCH CH224A, 24k on CFG1 = 12 V (datasheet tab. 5-1)","SMT",""
"R1","24k","Resistor_SMD:R_0603_1608Metric","24k 1% 0603","SMT",""
"C1","1uF 25V","Capacitor_SMD:C_0805_2012Metric","1uF 25V X7R","SMT",""
"J2","DC 6-20V","Connector_BarrelJack:BarrelJack_CUI_PJ-063AH_Horizontal","CUI PJ-063AH","hand",""
"D1","B540C","Diode_SMD:D_SMC","Diodes B540C-13-F","SMT",""
"D2","B540C","Diode_SMD:D_SMC","Diodes B540C-13-F","SMT",""
"D3","SMBJ22A","Diode_SMD:D_SMB","TVS SMBJ22A, cathode to CHG_IN","SMT",""
"U2","BQ25798","Package_DFN_QFN:Texas_RQM0029A_VQFN-29_4x4mm_P0.4mm","TI BQ25798RQMR","SMT",""
"L1","2.2uH","Inductor_SMD:L_Bourns_SRP7028A_7.3x6.6mm","2.2 uH >= 8 A sat, e.g. Bourns SRP7028A-2R2M","SMT",""
"C2","47nF 25V","Capacitor_SMD:C_0603_1608Metric","47nF 25V X7R","SMT",""
"C3","47nF 25V","Capacitor_SMD:C_0603_1608Metric","47nF 25V X7R","SMT",""
"C4","4.7uF 16V","Capacitor_SMD:C_0805_2012Metric","4.7uF 16V X7R","SMT",""
"C5","10uF 25V","Capacitor_SMD:C_1206_3216Metric","10uF 25V X7R","SMT",""
"C6","10uF 25V","Capacitor_SMD:C_1206_3216Metric","10uF 25V X7R","SMT",""
"C7","100nF 50V","Capacitor_SMD:C_0603_1608Metric","100nF 50V X7R","SMT",""
"C8","10uF 25V","Capacitor_SMD:C_1206_3216Metric","10uF 25V X7R","SMT",""
"C9","10uF 25V","Capacitor_SMD:C_1206_3216Metric","10uF 25V X7R","SMT",""
"C10","10uF 25V","Capacitor_SMD:C_1206_3216Metric","10uF 25V X7R","SMT",""
"C11","100nF 50V","Capacitor_SMD:C_0603_1608Metric","100nF 50V X7R","SMT",""
"C12","10uF 25V","Capacitor_SMD:C_1206_3216Metric","10uF 25V X7R","SMT",""
"C13","10uF 25V","Capacitor_SMD:C_1206_3216Metric","10uF 25V X7R","SMT",""
"C14","10uF 25V","Capacitor_SMD:C_1206_3216Metric","10uF 25V X7R","SMT",""
"C15","10uF 25V","Capacitor_SMD:C_1206_3216Metric","10uF 25V X7R","SMT",""
"C16","10uF 25V","Capacitor_SMD:C_1206_3216Metric","10uF 25V X7R","SMT",""
"C17","100nF 50V","Capacitor_SMD:C_0603_1608Metric","100nF 50V X7R","SMT",""
"C18","10uF 25V","Capacitor_SMD:C_1206_3216Metric","10uF 25V X7R","SMT",""
"C19","10uF 25V","Capacitor_SMD:C_1206_3216Metric","10uF 25V X7R","SMT",""
"R2","8.2k","Resistor_SMD:R_0603_1608Metric","8.2k 1% 0603: 750 kHz, 2S (datasheet 7.3.2)","SMT",""
"R3","100","Resistor_SMD:R_0603_1608Metric","100 1% 0603","SMT",""
"C20","1nF 50V","Capacitor_SMD:C_0603_1608Metric","1nF 50V X7R","SMT",""
"R4","5.23k","Resistor_SMD:R_0603_1608Metric","5.23k 1% 0603","SMT",""
"R5","30.1k","Resistor_SMD:R_0603_1608Metric","30.1k 1% 0603","SMT",""
"RT1","10k NTC 103AT","Resistor_SMD:R_0603_1608Metric","Semitec 103AT-2 or 10k B3435 0603, at the cells","SMT",""
"R6","10k","Resistor_SMD:R_0603_1608Metric","10k 1% 0603","SMT",""
"R7","1k","Resistor_SMD:R_0603_1608Metric","1k 1% 0603","SMT",""
"LED1","CHG","LED_SMD:LED_0603_1608Metric","0603 orange","SMT",""
"TP1","QON","TestPoint:TestPoint_Pad_D1.0mm","","SMT",""
"BT1","18650 low","Battery:BatteryHolder_Keystone_1042_1x18650","Keystone 1042 + 18650 cell (protected cell recommended)","hand",""
"BT2","18650 high","Battery:BatteryHolder_Keystone_1042_1x18650","Keystone 1042 + 18650 cell","hand",""
"F1","5A","Fuse:Fuse_1812_4532Metric","Littelfuse 1812L500 or SMD fuse 5 A 1812","SMT",""
"U3","BQ29209","Package_SON:VSON-8-1EP_3x3mm_P0.65mm_EP1.65x2.4mm","TI BQ29209DRBR: 2S OVP + balancing","SMT",""
"R8","1k","Resistor_SMD:R_0603_1608Metric","1k 1% 0603","SMT",""
"R9","1k","Resistor_SMD:R_0603_1608Metric","1k 1% 0603","SMT",""
"C21","100nF","Capacitor_SMD:C_0603_1608Metric","100nF X7R","SMT",""
"C22","100nF","Capacitor_SMD:C_0603_1608Metric","100nF X7R","SMT",""
"R10","910","Resistor_SMD:R_0603_1608Metric","910 5% 0603: ~3 mA balance current","SMT",""
"R11","100","Resistor_SMD:R_0603_1608Metric","100 1% 0603","SMT",""
"C23","100nF","Capacitor_SMD:C_0603_1608Metric","100nF X7R","SMT",""
"C24","100nF","Capacitor_SMD:C_0603_1608Metric","100nF X7R","SMT",""
"R12","100k","Resistor_SMD:R_0603_1608Metric","OUT high on cell overvoltage -> CE high -> no charging","SMT",""
"R13","47k","Resistor_SMD:R_0603_1608Metric","47k 1% 0603","SMT",""
"U4","TPS55340","Package_SO:Texas_HTSSOP-14-1EP_4.4x5mm_P0.65mm_EP3.4x5mm_Mask2.94x3.34mm_ThermalVias","TI TPS55340PWPR","SMT",""
"L2","10uH","Inductor_SMD:L_Bourns_SRP7028A_7.3x6.6mm","10 uH >= 6 A sat, e.g. Bourns SRP7028A-100M","SMT",""
"D4","B540C","Diode_SMD:D_SMC","Diodes B540C-13-F","SMT",""
"C25","10uF 25V","Capacitor_SMD:C_1206_3216Metric","10uF 25V X7R","SMT",""
"C26","10uF 25V","Capacitor_SMD:C_1206_3216Metric","10uF 25V X7R","SMT",""
"C27","100nF 50V","Capacitor_SMD:C_0603_1608Metric","100nF 50V X7R","SMT",""
"R14","100k","Resistor_SMD:R_0603_1608Metric","100k 1% 0603","SMT",""
"C28","47nF","Capacitor_SMD:C_0603_1608Metric","47nF X7R","SMT",""
"R15","78.7k","Resistor_SMD:R_0603_1608Metric","78.7k 1%: 600 kHz (datasheet 8.2.1.2.2)","SMT",""
"R16","2k","Resistor_SMD:R_0603_1608Metric","2k 1% 0603","SMT",""
"C29","100nF","Capacitor_SMD:C_0603_1608Metric","100nF X7R","SMT",""
"C30","100pF","Capacitor_SMD:C_0603_1608Metric","100pF X7R","SMT",""
"R17","88.7k","Resistor_SMD:R_0603_1608Metric","88.7k 1%: 12.13 V with 10k (eq. 24)","SMT",""
"R18","10k","Resistor_SMD:R_0603_1608Metric","10k 1% 0603","SMT",""
"C31","10uF 25V","Capacitor_SMD:C_1206_3216Metric","10uF 25V X7R","SMT",""
"C32","10uF 25V","Capacitor_SMD:C_1206_3216Metric","10uF 25V X7R","SMT",""
"C33","10uF 25V","Capacitor_SMD:C_1206_3216Metric","10uF 25V X7R","SMT",""
"C34","100uF 25V","Capacitor_SMD:CP_Elec_8x10","100 uF 25 V low-ESR electrolytic, 8x10","SMT",""
"U5","TPS259541","Package_SON:Texas_DSG0008A_WSON-8-1EP_2x2mm_P0.5mm_EP0.9x1.6mm","TI TPS259541DSGR: 13.7 V clamp, auto-retry","SMT",""
"C35","22nF","Capacitor_SMD:C_0603_1608Metric","22nF X7R","SMT",""
"R19","1.4k","Resistor_SMD:R_0603_1608Metric","1.40k 1%: ~1.5 A limit (datasheet ILIMIT table)","SMT",""
"R20","100k","Resistor_SMD:R_0603_1608Metric","100k 1% 0603","SMT",""
"R21","13.7k","Resistor_SMD:R_0603_1608Metric","UVLO ~10 V","SMT",""
"Q1","AO3400A","Package_TO_SOT_SMD:SOT-23","AO3400A: GPIO high = lens power off","SMT",""
"R22","100k","Resistor_SMD:R_0603_1608Metric","100k 1% 0603","SMT",""
"R23","10k","Resistor_SMD:R_0603_1608Metric","10k 1% 0603","SMT",""
"RS1","20mR","Resistor_SMD:R_2512_6332Metric","20 mOhm 1% 2512, 1 W","SMT",""
"U6","INA219","Package_TO_SOT_SMD:SOT-23-8","TI INA219AIDCNR (SOT-23-8: A1 A0 SDA SCL VS GND IN- IN+), addr 0x40","SMT",""
"C36","100nF","Capacitor_SMD:C_0603_1608Metric","100nF X7R","SMT",""
"C37","10uF 25V","Capacitor_SMD:C_1206_3216Metric","10uF 25V X7R","SMT",""
"U7","LM317","Package_TO_SOT_SMD:SOT-223-3_TabPin2","LM317 SOT-223","SMT",""
"R24","240","Resistor_SMD:R_0603_1608Metric","240 1% 0603","SMT",""
"R25","1.5k","Resistor_SMD:R_0603_1608Metric","9.06 V","SMT",""
"C38","1uF 25V","Capacitor_SMD:C_0805_2012Metric","1uF 25V X7R","SMT",""
"C39","10uF 25V","Capacitor_SMD:C_1206_3216Metric","10uF 25V X7R","SMT",""
"U8","AP63205","Package_TO_SOT_SMD:SOT-23-6","Diodes AP63205WU-7 (FB VOUT, EN, VIN, GND, SW, BST)","SMT",""
"L3","4.7uH","Inductor_SMD:L_Bourns-SRN4018","4.7 uH >= 3 A, e.g. Bourns SRN4018-4R7M","SMT",""
"C40","100nF","Capacitor_SMD:C_0603_1608Metric","100nF X7R","SMT",""
"C41","10uF 25V","Capacitor_SMD:C_1206_3216Metric","10uF 25V X7R","SMT",""
"C42","22uF 10V","Capacitor_SMD:C_1206_3216Metric","22uF 10V X7R","SMT",""
"C43","22uF 10V","Capacitor_SMD:C_1206_3216Metric","22uF 10V X7R","SMT",""
"D5","BAT60A","Diode_SMD:D_SOD-323","Schottky 1 A SOD-323: no back-feed from the ESP32's USB","SMT",""
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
